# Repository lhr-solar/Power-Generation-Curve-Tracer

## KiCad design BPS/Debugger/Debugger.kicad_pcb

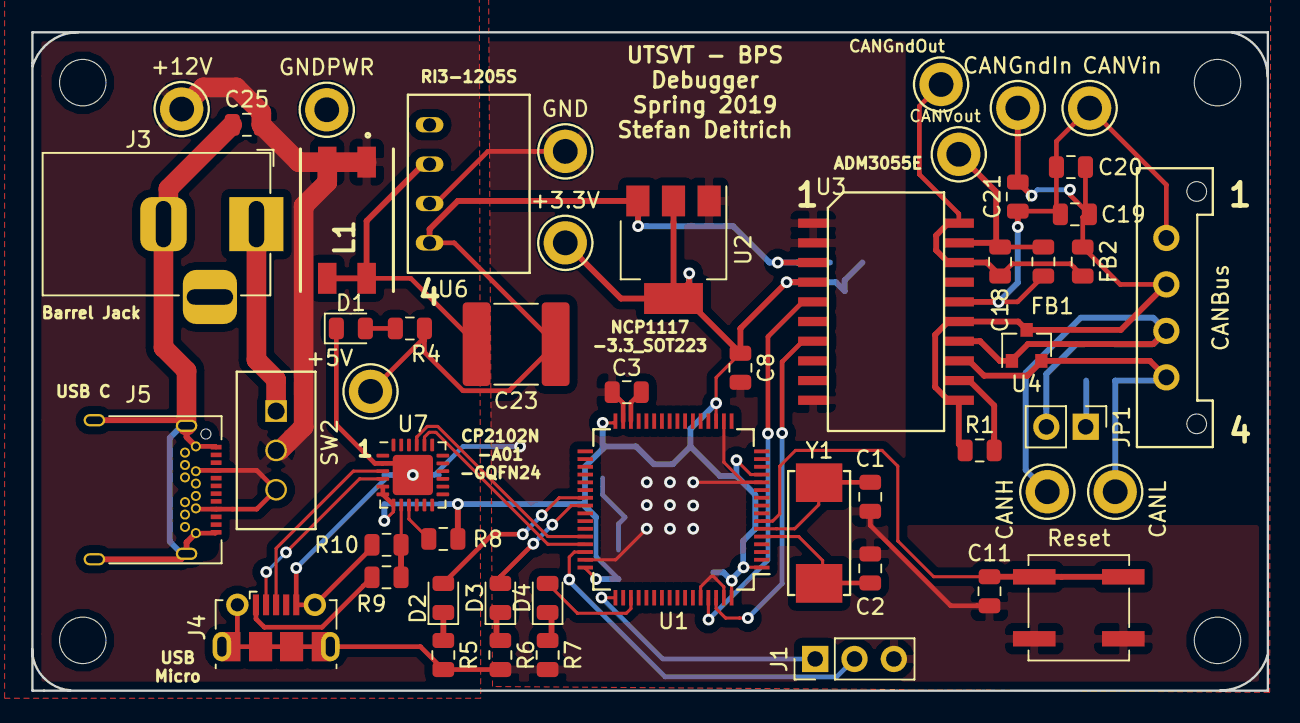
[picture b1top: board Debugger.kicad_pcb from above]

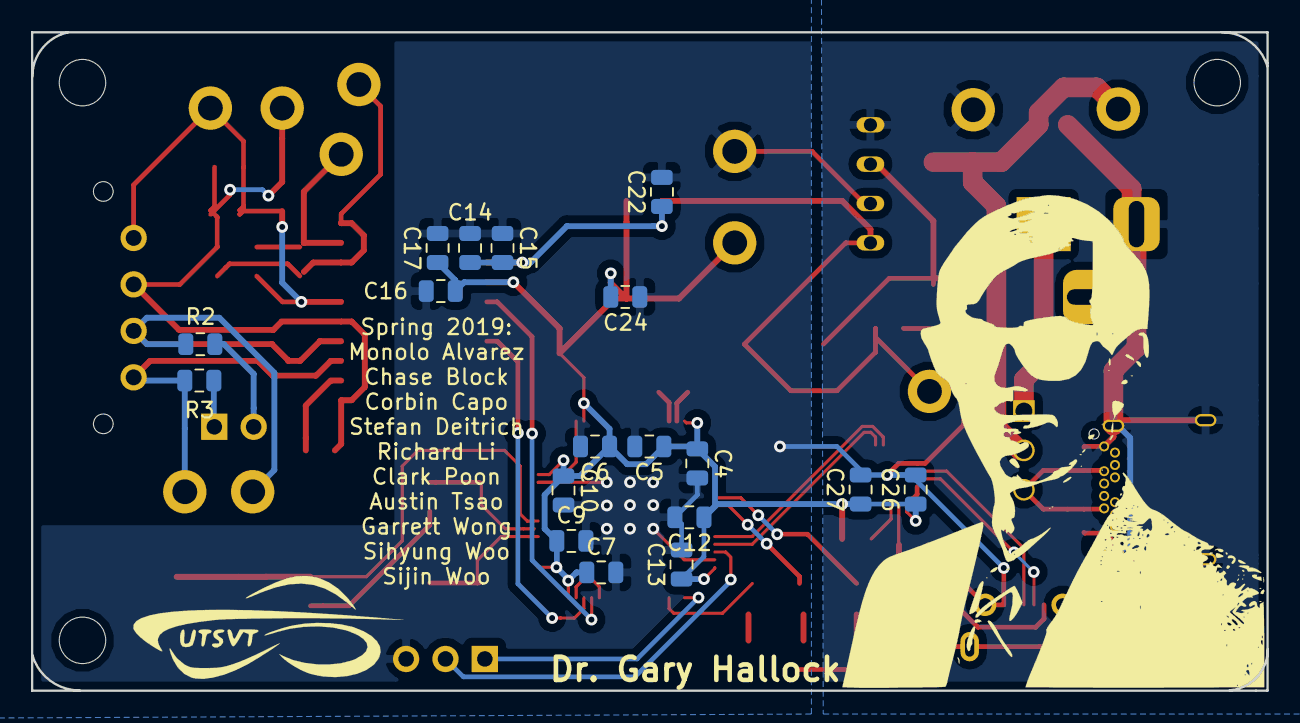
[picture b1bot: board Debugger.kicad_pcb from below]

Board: 2 copper layers, 79.8 x 42.5 mm, 74 parts (18 on the bottom side), 39 nets.

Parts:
+3.3V: +3.3V_TP; TestPoint_Keystone_5005-5009_Compact
+5V: +5V_TP; TestPoint_Keystone_5005-5009_Compact
+12V: +12V_TP; TestPoint_Keystone_5005-5009_Compact
C1, C2: 6pF; C_0805_2012Metric
C3: 2.2 uF; C_0805_2012Metric
C4, C5, C6, C7, C9, C10, C11, C12, C14, C15, C16, C17, C20, C22, C27: 0.1uF; C_0805_2012Metric
C8: 1uF; C_0805_2012Metric
C13, C25, C26: 4.7uF; C_0805_2012Metric
C18: 10uf; C_0805_2012Metric
C19: 0.22uF; C_0805_2012Metric
C21: 0.01uF; C_0805_2012Metric
C23: 470pF; C_2220_5650Metric
C24: 10uF; C_0805_2012Metric
CANBus: CAN_Out; Molex_MicroFit3.0_1x4xP3.00mm_PolarizingPeg_Vertical
CANGndIn: CAN_ISO_GndIn; TestPoint_Keystone_5005-5009_Compact
CANGndOut: CAN_ISO_GndOut; TestPoint_Keystone_5005-5009_Compact
CANH: CAN_ISO_GndIn; TestPoint_Keystone_5005-5009_Compact
CANL: CAN_ISO_GndOut; TestPoint_Keystone_5005-5009_Compact
CANVin: CAN_ISO_Vin; TestPoint_Keystone_5005-5009_Compact
CANVout: CAN_ISO_Vout; TestPoint_Keystone_5005-5009_Compact
D1, D2, D3, D4: LED; LED_0805_2012Metric
FB1, FB2: Ferrite_Bead_Small; L_0805_2012Metric
GND: GND_TP; TestPoint_Keystone_5005-5009_Compact
GNDPWR: GNDPWR_TP; TestPoint_Keystone_5005-5009_Compact
J1: Conn_01x03; PinHeader_1x03_P2.54mm_Vertical
J3: Barrel_Jack; BarrelJack_Horizontal
J4: USB_B_Micro; USB_Micro-B_Molex-105017-0001
J5: USB_C_Receptacle; USB_C_Receptacle_Amphenol_12401548E4-2A
JP1: Termination Resistors; PinHeader_1x02_P2.54mm_Vertical
L1: 10uH; SRF0905A
MH1, MH2, MH3, MH4: MountingHole; MountingHole_3mm
R1: 0; R_0805_2012Metric
R2, R3: 60; R_0805_2012Metric
R4: 1.5k; R_0805_2012Metric
R5, R6, R7: 750; R_0805_2012Metric
R8: 1k; R_0805_2012Metric
R9: 22.1k; R_0805_2012Metric
R10: 47.5k; R_0805_2012Metric
Reset: Switch:SW_Push; SW_SPST_B3SL-1002P
SW2: SW_SPDT; TS01CQE
U1: STM32F413RHTx; LQFP-64_10x10mm_P0.5mm
U2: NCP1117-3.3_SOT223; SOT-223-3_TabPin2
U3: ADM3055E; SOIC-20W_7.5x15.4mm_Pitch1.27mm
U4: CDSOT23-T24CAN; SOT-23
U6: RI3-1205S; RI3_DC_Converter
U7: CP2102N-A01-GQFN24; QFN-24-1EP_4x4mm_P0.5mm_EP2.6x2.6mm
Y1: Crystal; NX8045GB-8.000M-STD-CSJ-1

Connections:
+3V3: +3.3V.1, C4.1, C5.1, C6.1, C7.1, C8.1, C9.1, C10.1, C12.1, C13.1, C16.1, C17.1, C24.1, C26.1, C27.1, R8.1, U1.1, U1.13, U1.19, U1.32, U1.48, U1.64, U2.2, U3.4, U7.5, U7.6, U7.7
+5V: +5V.1, C14.1, C15.1, C22.1, C23.1, R4.1, U2.3, U3.3, U6.4
+12V: +12V.1, C25.1, L1.1, L1.2, SW2.2
/CAN1_RX: U1.61, U3.5
/CAN1_TX: U1.62, U3.7
/CAN/CAN_H: CANBus.3, CANH.1, R2.2, U3.14, U4.1
/CAN/CAN_L: CANBus.4, CANL.1, R3.1, U3.13, U4.2
/CAN/RSlope: R1.2, U3.12
/CAN/TERM_H: JP1.2, R2.1
/CAN/TERM_L: JP1.1, R3.2
/NRST: C11.1, Reset.1, U1.7
/OSC_IN: C2.1, U1.5, Y1.2
/OSC_OUT: C1.1, U1.6, Y1.1
/PC8: D2.2, U1.39
/PC9: D3.2, U1.40
/PC10: D4.2, U1.51
/SWCLK: J1.1, U1.49
/SWDIO: J1.2, U1.46
/USB_RX: U1.44, U7.21
/USB_TX: U1.45, U7.20
GND: C1.2, C2.2, C3.2, C4.2, C5.2, C6.2, C7.2, C8.2, C9.2, C10.2, C11.2, C12.2, C13.2, C14.2, C15.2, C16.2, C17.2, C22.2, C24.2, C26.2, C27.2, D1.1, GND.1, J1.3, J4.5, J4.6, R5.2, R6.2, R7.2, R10.2, Reset.2, U1.12, U1.18, U1.31, U1.47, U1.60, U1.63, U2.1, U3.1, U3.2, U3.10, U6.3, U7.2, U7.25
GNDPWR: C25.2, GNDPWR.1, J3.2, J5.A1, J5.A12, J5.B1, J5.B12, J5.S1, U6.1
unnamed: C3.1, U1.30
unnamed: C18.1, CANVout.1, FB1.1, U3.19
unnamed: C18.2, CANGndOut.1, FB2.2, U3.18, U3.20
unnamed: C19.1, C20.1, C21.1, CANBus.1, CANVin.1, FB1.2, U3.16
unnamed: C19.2, C20.2, C21.2, CANBus.2, CANGndIn.1, FB2.1, R1.1, U3.11, U3.15, U4.3
unnamed: C23.2, L1.3, L1.4, U6.2
unnamed: D1.2, R4.2
unnamed: D2.1, R5.1
unnamed: D3.1, R6.1
unnamed: D4.1, R7.1
unnamed: J3.1, SW2.1
unnamed: J4.1, R9.2
unnamed: J4.2, U7.4
unnamed: J4.3, U7.3
unnamed: J5.A4, J5.A9, J5.B4, J5.B9, SW2.3
unnamed: R8.2, U7.9
unnamed: R9.1, R10.1, U7.8

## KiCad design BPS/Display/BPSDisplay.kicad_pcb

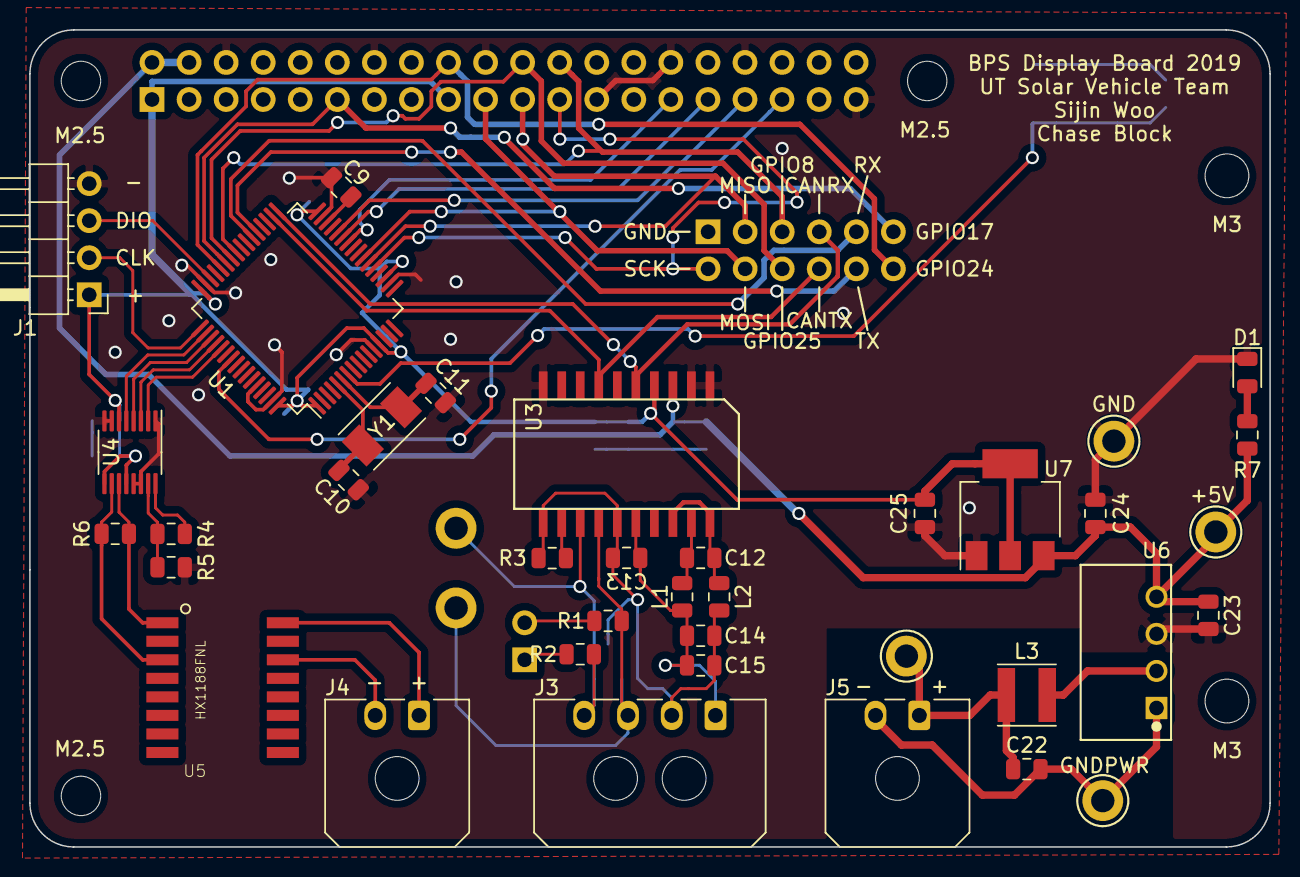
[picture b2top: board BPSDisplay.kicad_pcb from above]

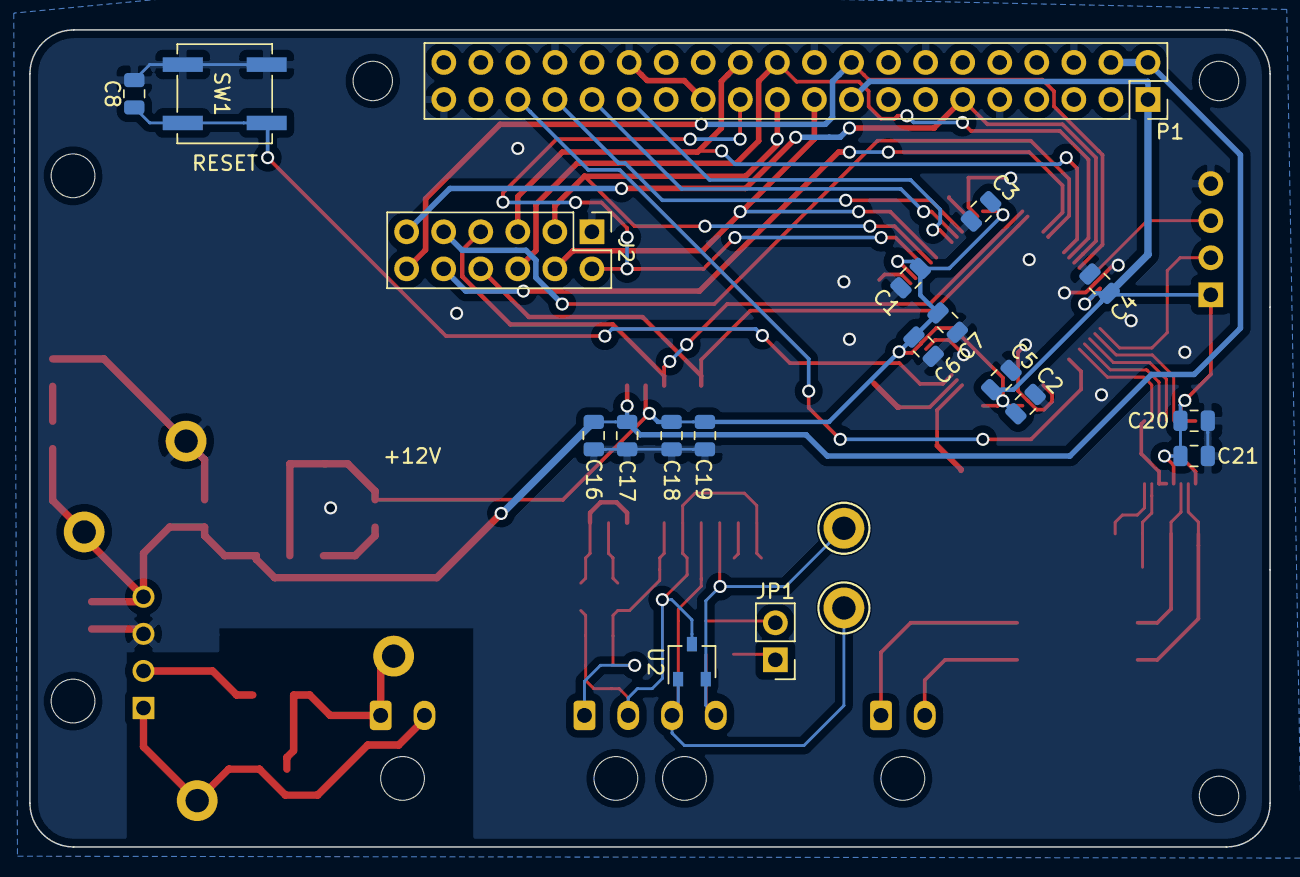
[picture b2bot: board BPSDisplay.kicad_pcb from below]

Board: 2 copper layers, 85.0 x 56.0 mm, 63 parts (21 on the bottom side), 47 nets.

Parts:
C1, C2, C3, C4, C6, C8, C20, C21: 0.1u; C_0805_2012Metric
C5, C22, C23: 4.7u; C_0805_2012Metric
C7: 1u; C_0805_2012Metric
C9: 2.2u; C_0805_2012Metric
C10, C11: 8p; C_0805_2012Metric
C12: 0.22uF; C_0805_2012Metric
C13, C16: 10uF; C_0805_2012Metric
C14, C17, C18: 0.1uF; C_0805_2012Metric
C15, C19: 0.01uF; C_0805_2012Metric
C24, C25: 10u; C_0805_2012Metric
D1: PowerOn; LED_0805_2012Metric
J1: SWD; PinHeader_1x04_P2.54mm_Horizontal
J2: Conn_02x06_Counter_Clockwise; PinHeader_2x06_P2.54mm_Vertical
J3: CAN_Out; Molex_Micro-Fit_3.0_43650-0400_1x04_P3.00mm_Horizontal
J4: isoSPI_Display; Molex_Micro-Fit_3.0_43650-0200_1x02_P3.00mm_Horizontal
J5: CarPowerConnector; Molex_Micro-Fit_3.0_43650-0200_1x02_P3.00mm_Horizontal
JP1: Termination Resistors; PinHeader_1x02_P2.54mm_Vertical
L1, L2: 2kH; L_0805_2012Metric
L3: 6.8u; L_Taiyo-Yuden_MD-4040
MK1, MK2, MK4: M2.5; MountingHole_2.7mm_M2.5
MK3, MK5: M3; MountingHole_3mm
P1: Conn_02x20_Odd_Even; PinSocket_2x20_P2.54mm_Vertical
R1, R2: 60; R_0805_2012Metric
R3: 0; R_0805_2012Metric
R4: 806; R_0805_2012Metric
R5: 1.21k; R_0805_2012Metric
R6: 120; R_0805_2012Metric
R7: 1.5k; R_0805_2012Metric
SW1: Reset; SW_SPST_B3SL-1002P
TP1: CAN_H; TestPoint_Keystone_5005-5009_Compact
TP2: CAN_L; TestPoint_Keystone_5005-5009_Compact
TP3: +3.3V_TP; TestPoint_Keystone_5005-5009_Compact
TP4: +12V_TP; TestPoint_Keystone_5005-5009_Compact
TP5: GNDPWR_TP; TestPoint_Keystone_5005-5009_Compact
TP6: GND_TP; TestPoint_Keystone_5005-5009_Compact
U1: STM32F413RHTx; LQFP-64_10x10mm_P0.5mm
U2: CDSOT23-T24CAN; SOT-23W
U3: ADM3055E; SOIC-20W_7.5x15.4mm_Pitch1.27mm
U4: LTC6820; MSOP-16_3x4mm_P0.5mm
U5: HX1188FNL; HXXXX
U6: PDS1-S12-S5; PDSx-S
U7: NCP1117-3.3_SOT223; SOT-223-3_TabPin2
Y1: 8M; Crystal_SMD_TXC_7A-2Pin_5x3.2mm

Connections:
+3V3: C1.1, C2.1, C3.1, C4.1, C5.1, C6.1, C7.1, C18.1, C19.1, C20.1, C21.1, C25.1, J1.1, P1.1, P1.17, U1.1, U1.13, U1.19, U1.32, U1.48, U1.64, U3.4, U4.6, U4.9, U4.12, U7.2
+5V: C16.1, C17.1, C23.1, C24.1, P1.2, P1.4, R7.1, TP3.1, U3.3, U6.4, U7.3
+12V: C22.1, J5.1, L3.1, TP4.1
/CAN2_RX: J2.7, U1.33, U3.5
/CAN2_TX: J2.8, U1.34, U3.7
/CAN/CAN_H: J3.3, R1.2, TP1.1, U2.1, U3.14
/CAN/CAN_L: J3.4, R2.2, TP2.1, U2.2, U3.13
/CAN/RSlope: R3.1, U3.12
/CAN/TERM_H: JP1.2, R1.1
/CAN/TERM_L: JP1.1, R2.1
/DISPCS: U1.50, U4.5
/GPIO5: P1.29, U1.26
/GPIO6: P1.31, U1.27
/GPIO8(SPI0_CE_N): J2.5, P1.24, U1.41
/GPIO9(SPI0_MISO): J2.3, P1.21, U1.22
/GPIO10(SPI0_MOSI): J2.4, P1.19, U1.23
/GPIO11(SPI0_SCK): J2.2, P1.23, U1.21
/GPIO13: P1.33, U1.28
/GPIO17(GEN0): J2.11, P1.11, U1.43
/GPIO19: P1.35, U1.55
/GPIO24(GEN5): J2.12, P1.18, U1.44
/GPIO25(GEN6): J2.6, P1.22, U1.42
/NRST: C8.1, SW1.1, U1.7
/SPI3_MISO: U1.52, U4.3
/SPI3_MOSI: U1.53, U4.2
/SPI3_SCK: U1.51, U4.4
/SWCLK: J1.2, U1.49
/SWDIO: J1.3, U1.46
/USART6_RX: J2.9, U1.38
/USART6_TX: J2.10, U1.37
/isoSPI/DISP_IM: R6.1, U4.10, U5.3
/isoSPI/DISP_IP: R6.2, U4.11, U5.1
GND: C1.2, C2.2, C3.2, C4.2, C5.2, C6.2, C7.2, C8.2, C9.2, C10.2, C11.2, C16.2, C17.2, C18.2, C19.2, C20.2, C21.2, C23.2, C24.2, C25.2, D1.1, J1.4, J2.1, P1.6, P1.9, P1.14, P1.20, P1.25, P1.30, P1.34, P1.39, R5.1, SW1.2, TP6.1, U1.12, U1.18, U1.31, U1.47, U1.60, U1.63, U3.1, U3.2, U3.10, U4.1, U4.7, U4.8, U4.13, U4.14, U6.3, U7.1
GNDPWR: C22.2, J5.2, TP5.1, U6.1
unnamed: C9.1, U1.30
unnamed: C10.1, U1.5, Y1.1
unnamed: C11.1, U1.6, Y1.2
unnamed: C12.1, L1.2, U3.19
unnamed: C12.2, L2.2, U3.18, U3.20
unnamed: C13.1, C14.1, C15.1, J3.1, L1.1, U3.16
unnamed: C13.2, C14.2, C15.2, J3.2, L2.1, R3.2, U2.3, U3.11, U3.15
unnamed: D1.2, R7.2
unnamed: J4.1, U5.16
unnamed: J4.2, U5.14
unnamed: L3.2, U6.2
unnamed: R4.1, R5.2, U4.15
unnamed: R4.2, U4.16

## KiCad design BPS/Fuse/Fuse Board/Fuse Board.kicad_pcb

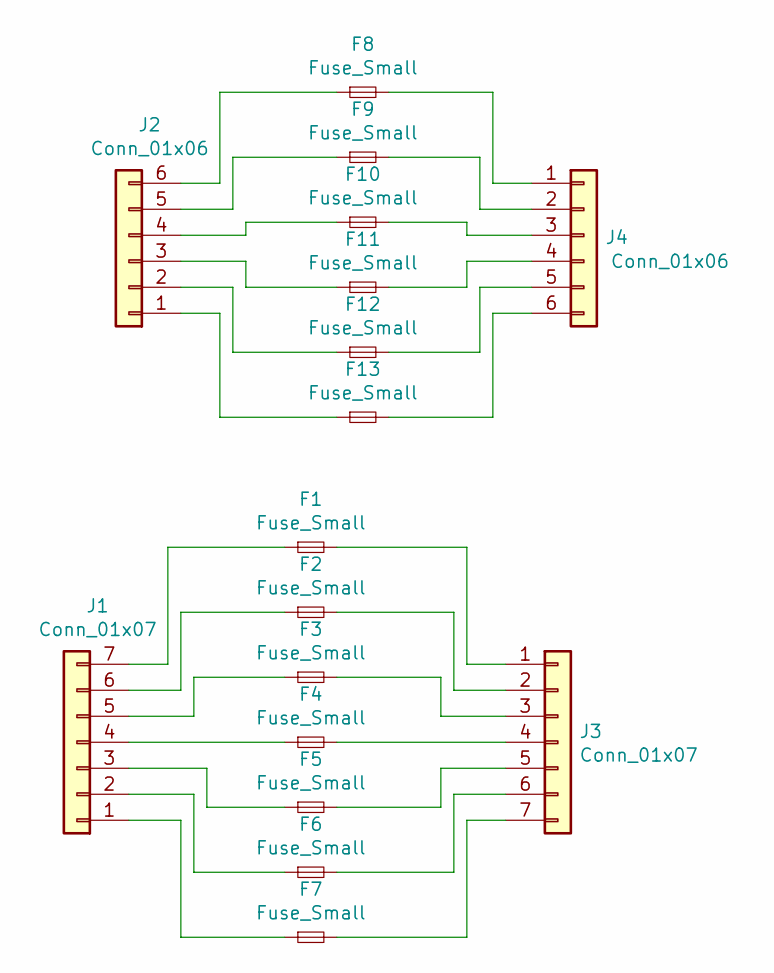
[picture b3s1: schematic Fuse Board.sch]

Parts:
F1, F2, F3, F4, F5, F6, F7, F8, F9, F10, F11, F12, F13: Fuse_Small; MSF 250 Fuse
J1, J3: Conn_01x07; Molex_MicroFit_01x07_Horizontal
J2, J4: Conn_01x06; Molex_MicroFit_01x06_Horizontal

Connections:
unnamed: F1.1, J1.7
unnamed: F1.2, J3.1
unnamed: F2.1, J1.6
unnamed: F2.2, J3.2
unnamed: F3.1, J1.5
unnamed: F3.2, J3.3
unnamed: F4.1, J1.4
unnamed: F4.2, J3.4
unnamed: F5.1, J1.3
unnamed: F5.2, J3.5
unnamed: F6.1, J1.2
unnamed: F6.2, J3.6
unnamed: F7.1, J1.1
unnamed: F7.2, J3.7
unnamed: F8.1, J2.6
unnamed: F8.2, J4.1
unnamed: F9.1, J2.5
unnamed: F9.2, J4.2
unnamed: F10.1, J2.4
unnamed: F10.2, J4.3
unnamed: F11.1, J2.3
unnamed: F11.2, J4.4
unnamed: F12.1, J2.2
unnamed: F12.2, J4.5
unnamed: F13.1, J2.1
unnamed: F13.2, J4.6

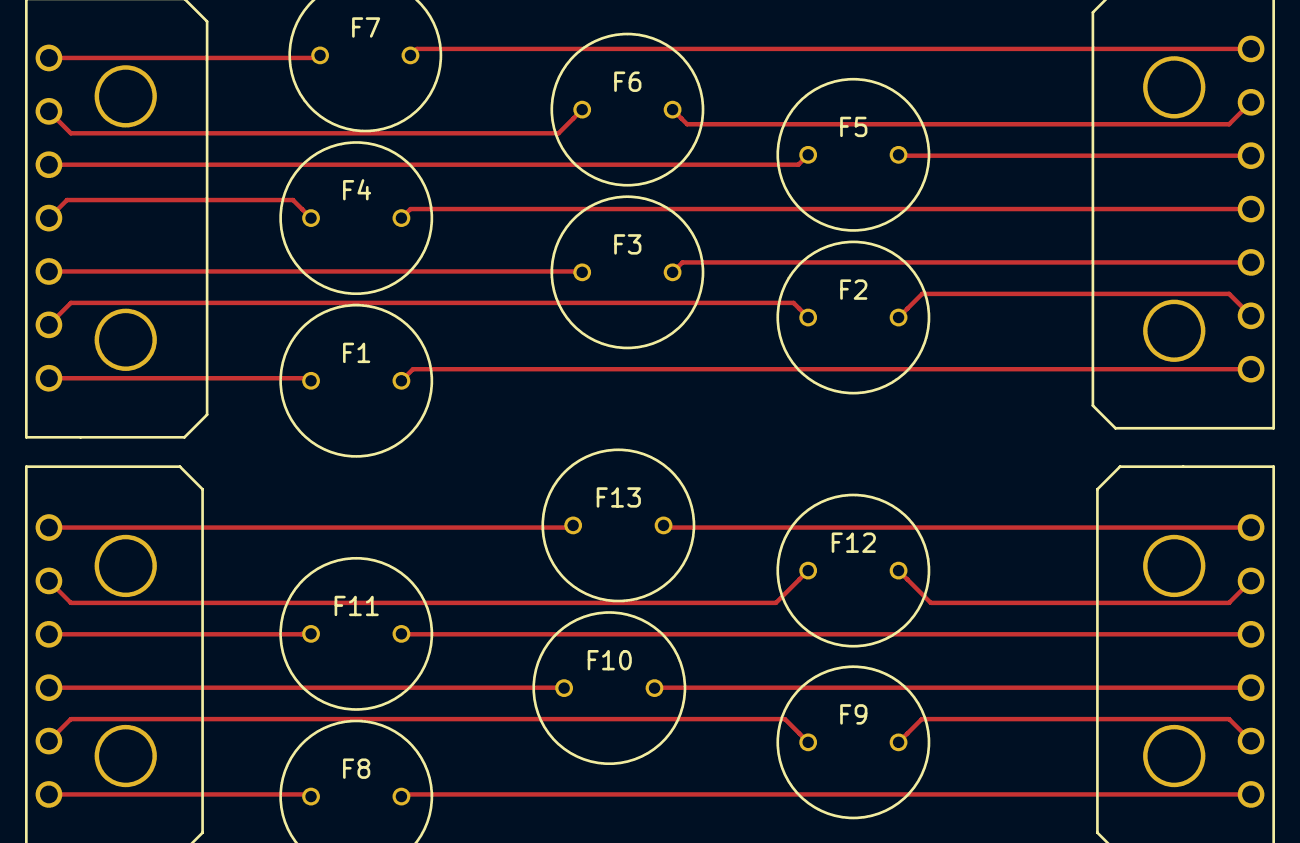
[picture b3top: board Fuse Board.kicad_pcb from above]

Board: 2 copper layers, 17 parts (0 on the bottom side), 26 nets.

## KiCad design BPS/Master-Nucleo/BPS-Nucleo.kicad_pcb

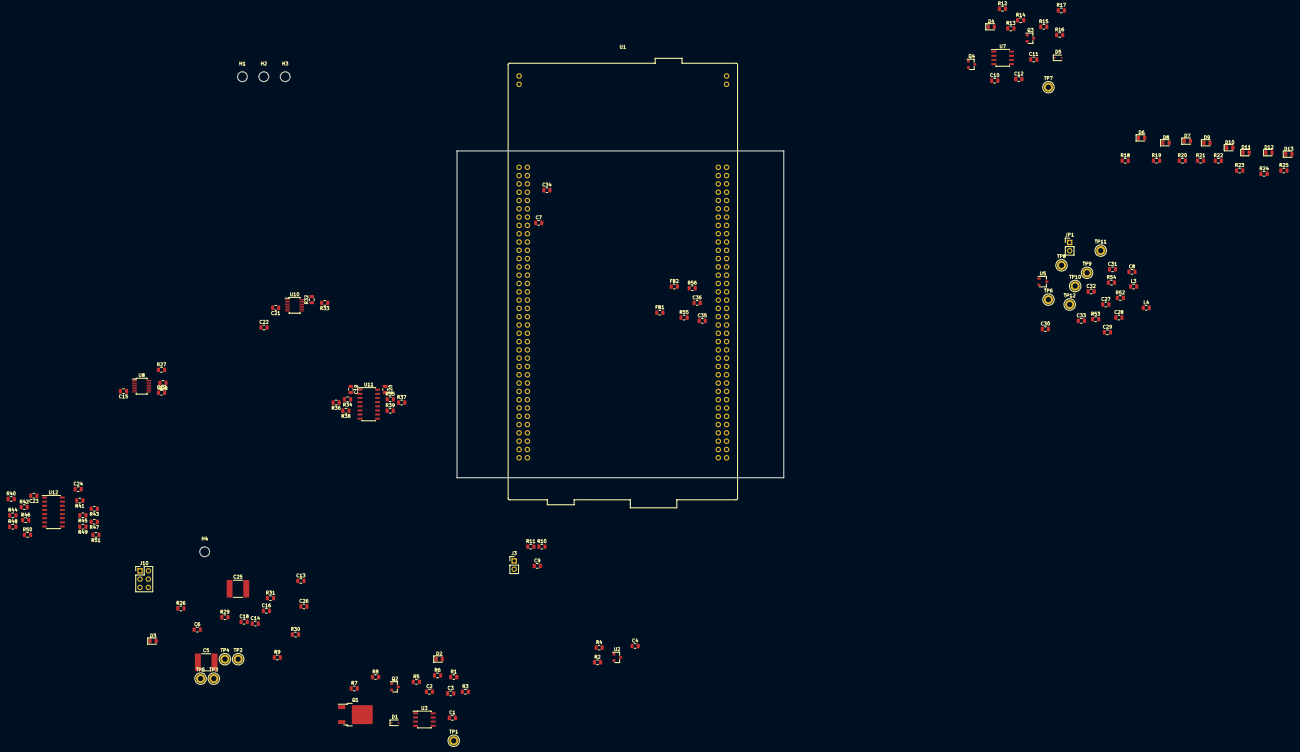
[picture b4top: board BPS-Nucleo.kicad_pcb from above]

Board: 2 copper layers, 141 parts (0 on the bottom side), 97 nets, no tracks yet.

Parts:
C1, C4, C10: 1uF; C_0805_2012Metric
C2, C11, C27, C30: 10uF; C_0805_2012Metric
C3, C7, C9, C12, C15, C17, C19, C20, C21, C22, C23, C24, C28, C31, C32, C34: 0.1uF; C_0805_2012Metric
C5, C25: 470pF; C_2220_5650Metric
C6, C26: 4.7uF; C_0805_2012Metric
C8: 0.22uF; C_0805_2012Metric
C13, C14, C16, C18, C29, C33: 0.01uF; C_0805_2012Metric
C35, C36: 1u; C_0805_2012Metric
D1, D5: 1N4148WS; D_SOD-323
D2: ContactorEn; LED_0805_2012Metric
D3: PowerOn; LED_0805_2012Metric
D4: Fault; LED_0805_2012Metric
D6: Heartbeat; LED_0805_2012Metric
D7: UVolt; LED_0805_2012Metric
D8: OVolt; LED_0805_2012Metric
D9: OTemp; LED_0805_2012Metric
D10: OCurr; LED_0805_2012Metric
D11: WDError; LED_0805_2012Metric
D12: CANError; LED_0805_2012Metric
D13: Extra; LED_0805_2012Metric
FB1, FB2: 600; L_0805_2012Metric
H1, H2, H3, H4: MountingHole; MountingHole_3mm
J3: Conn_01x03; PinHeader_1x02_P2.54mm_Vertical
J10: DisplayJumper; PinHeader_2x03_P2.54mm_Vertical
JP1: Termination Resistors; PinHeader_1x02_P2.54mm_Vertical
L3, L4: 2kH; L_0805_2012Metric
Q1: VND5N07-E; TO-252-2
Q2, Q3, Q4: NTR4003NT1G; SOT-23
R1, R9: 1.5k; R_0805_2012Metric
R2, R10, R11: 4.7k; R_0805_2012Metric
R3, R12: 470; R_0805_2012Metric
R4: 1k; R_0805_2012Metric
R5, R7, R14, R16, R54: 0; R_0805_2012Metric
R6, R8, R15, R17: 10k; R_0805_2012Metric
R13: 1.6k; R_0805_2012Metric
R18: 680; R_0805_2012Metric
R19, R20, R21, R22, R23, R24, R25: 750; R_0805_2012Metric
R26, R29, R30, R31: 49.9; R_0805_2012Metric
R27, R32: 806; R_0805_2012Metric
R28, R33: 1.21k; R_0805_2012Metric
R34, R35, R36, R37, R38, R39, R40, R41, R42, R43, R44, R45, R46, R47, R48, R49, R50, R51: 50; R_0805_2012Metric
R52, R53: 60; R_0805_2012Metric
R55, R56: 220k; R_0805_2012Metric
TP1: ContactorGate_TP; TestPoint_Keystone_5005-5009_Compact
TP2: +12V_TP; TestPoint_Keystone_5005-5009_Compact
TP3: +5V_TP; TestPoint_Keystone_5005-5009_Compact
TP4: GNDPWR_TP; TestPoint_Keystone_5005-5009_Compact
TP5: GND_TP; TestPoint_Keystone_5005-5009_Compact
TP6: CAN_ISO_Vout; TestPoint_Keystone_5005-5009_Compact
TP7: StrobeLightGate_TP; TestPoint_Keystone_5005-5009_Compact
TP8: CAN_ISO_Vin; TestPoint_Keystone_5005-5009_Compact
TP9: CAN_ISO_GndIn; TestPoint_Keystone_5005-5009_Compact
TP10: CAN_ISO_GndOut; TestPoint_Keystone_5005-5009_Compact
TP11: CAN_H; TestPoint_Keystone_5005-5009_Compact
TP12: CAN_L; TestPoint_Keystone_5005-5009_Compact
U1: NUCLEO144-F412ZG; ST_Morpho_Connector_144_STLink
U2: BAS70-04; SOT-23
U3, U7: SI8261ABC-IS; SOIC-8_3.9x4.9mm_P1.27mm
U5: CDSOT23-T24CAN; SOT-23W
U8, U10: LTC6820; MSOP-16_3x4mm_P0.5mm
U11: Si8641EC-B-IS1; SOIC-16_3.9x9.9mm_P1.27mm
U12: SI8660EC-B-IS1; SOIC-16_3.9x9.9mm_P1.27mm

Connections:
+3V3: C7.2, C9.1, C15.1, C21.1, C32.1, C33.1, J10.1, J10.2, R10.1, R11.1, U1.16, U8.6, U8.7, U8.8, U10.6
+5V: C5.2, C17.1, C19.1, C22.1, C23.1, C30.1, C31.1, C34.1, D4.2, R1.1, R2.2, R3.2, R9.1, R12.2, TP3.1, U1.6, U2.2, U8.9, U8.12, U10.9, U10.12, U11.1, U11.7, U12.1
+5VL: C20.1, C24.1, C25.2, U11.10, U11.16, U12.16
+12V: C1.2, C2.1, C3.1, C6.1, C10.2, C11.1, C12.1, C26.1, D1.1, D5.1, TP2.1, U3.8, U7.8
/ADC1_CH2: C36.2, R56.2, U1.107
/ADC1_CH3: C35.2, R55.2, U1.109
/CAN/CAN_H: R52.2, TP11.1, U5.1
/CAN/CAN_L: R53.2, TP12.1, U5.2
/CAN/TERM_H: JP1.2, R52.1
/CAN/TERM_L: JP1.1, R53.1
/Contactor Driver/CONTACTOR_V-: D1.2, Q1.2
/DISPLAY_CS: U1.21, U10.5
/FAULT: R16.2, U1.88
/I2C3_SCL: J3.1, R10.2, U1.95
/I2C3_SDA: J3.2, R11.2, U1.73
/LTC6811_CS: U1.89, U8.5
/PA5: D13.2, U1.83
/PA6: D12.2, U1.85
/PA7: D11.2, U1.87
/PB0: R7.2, U1.34
/PB1: C4.1, R4.1, U1.96, U2.3
/PC0: D10.2, U1.38
/PC1: D9.2, U1.36
/PC2: D8.2, U1.35
/PC3: D7.2, U1.37
/RUN: D6.2, U1.28
/SPI1_CLK: R34.2, U1.103, U8.4, U10.4
/SPI1_MISO: R38.2, U1.99, U8.3, U10.3
/SPI1_MOSI: R36.2, U1.101, U8.2, U10.2
/SPI/DISP_IM: R31.1, U10.10
/SPI/DISP_IP: R30.1, U10.11
/SPI/DISP_PHA: J10.4, U10.8
/SPI/DISP_POL: J10.3, U10.7
/SPI/VOLT_IM: R29.1, U8.10
/SPI/VOLT_IP: R26.1, U8.11
/TEMP_CS1: R40.1, U1.102
/TEMP_CS2: R42.1, U1.100
/TEMP_CS3: R44.1, U1.98
/TEMP_CS4: R46.1, U1.76
/TEMP_CS5: R48.1, U1.91
/TEMP_CS6: R50.1, U1.74
GND: C4.2, C7.1, C9.2, C13.2, C14.2, C15.2, C16.2, C17.2, C18.2, C19.2, C21.2, C22.2, C23.2, C30.2, C31.2, C32.2, C33.2, C34.2, C35.1, C36.1, D3.1, J10.5, J10.6, Q2.2, Q4.2, R8.2, R17.2, R18.2, R19.2, R20.2, R21.2, R22.2, R23.2, R24.2, R25.2, R28.1, R33.1, TP5.1, U1.8, U1.19, U1.20, U1.22, U1.49, U1.60, U1.71, U1.72, U1.81, U1.92, U1.104, U1.111, U1.126, U1.135, U1.143, U1.144, U2.1, U8.1, U8.13, U8.14, U10.1, U10.13, U10.14, U11.2, U11.8, U12.8
GNDPWR: C1.1, C2.2, C3.2, C6.2, C10.1, C11.2, C12.2, C26.2, Q1.3, Q3.2, R6.2, R15.2, TP4.1, U3.5, U7.5
GND_A: C20.2, C24.2, U11.9, U11.15, U12.9
unnamed: C8.1, L3.2, TP6.1
unnamed: C8.2, L4.2, TP10.1
unnamed: C14.1, R26.2, R29.2
unnamed: C18.1, R30.2, R31.2
unnamed: C27.1, C28.1, C29.1, L3.1, TP8.1
unnamed: C27.2, C28.2, C29.2, L4.1, R54.2, TP9.1, U5.3
unnamed: D2.1, Q2.3, U3.3
unnamed: D2.2, R1.2
unnamed: D3.2, R9.2
unnamed: D4.1, R13.1
unnamed: D5.2, Q3.3
unnamed: D6.1, R18.1
unnamed: D7.1, R19.1
unnamed: D8.1, R20.1
unnamed: D9.1, R21.1
unnamed: D10.1, R22.1
unnamed: D11.1, R23.1
unnamed: D12.1, R24.1
unnamed: D13.1, R25.1
unnamed: FB1.2, R55.1
unnamed: FB2.2, R56.1
unnamed: R2.1, R4.2
unnamed: Q1.1, R5.1, R6.1
unnamed: Q2.1, R7.1, R8.1
unnamed: Q3.1, R14.1, R15.1
unnamed: Q4.1, R16.1, R17.1
unnamed: Q4.3, R13.2, U7.3
unnamed: R3.1, U3.2
unnamed: R5.2, TP1.1, U3.6
unnamed: R12.1, U7.2
unnamed: R14.2, TP7.1, U7.6
unnamed: R27.1, R28.2, U8.15
unnamed: R27.2, U8.16
unnamed: R32.1, R33.2, U10.15
unnamed: R32.2, U10.16
unnamed: R34.1, U11.3
unnamed: R35.1, U11.14
unnamed: R36.1, U11.4
unnamed: R37.1, U11.13
unnamed: R38.1, U11.6
unnamed: R39.1, U11.11
unnamed: R40.2, U12.2
unnamed: R41.2, U12.15
unnamed: R42.2, U12.3
unnamed: R43.2, U12.14
unnamed: R44.2, U12.4
unnamed: R45.2, U12.13
unnamed: R46.2, U12.5
unnamed: R47.2, U12.12
unnamed: R48.2, U12.6
unnamed: R49.2, U12.11
unnamed: R50.2, U12.7
unnamed: R51.2, U12.10

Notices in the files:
parts and their libraries:
Copyright 2016 Accelerated Designs. All rights reserved.
